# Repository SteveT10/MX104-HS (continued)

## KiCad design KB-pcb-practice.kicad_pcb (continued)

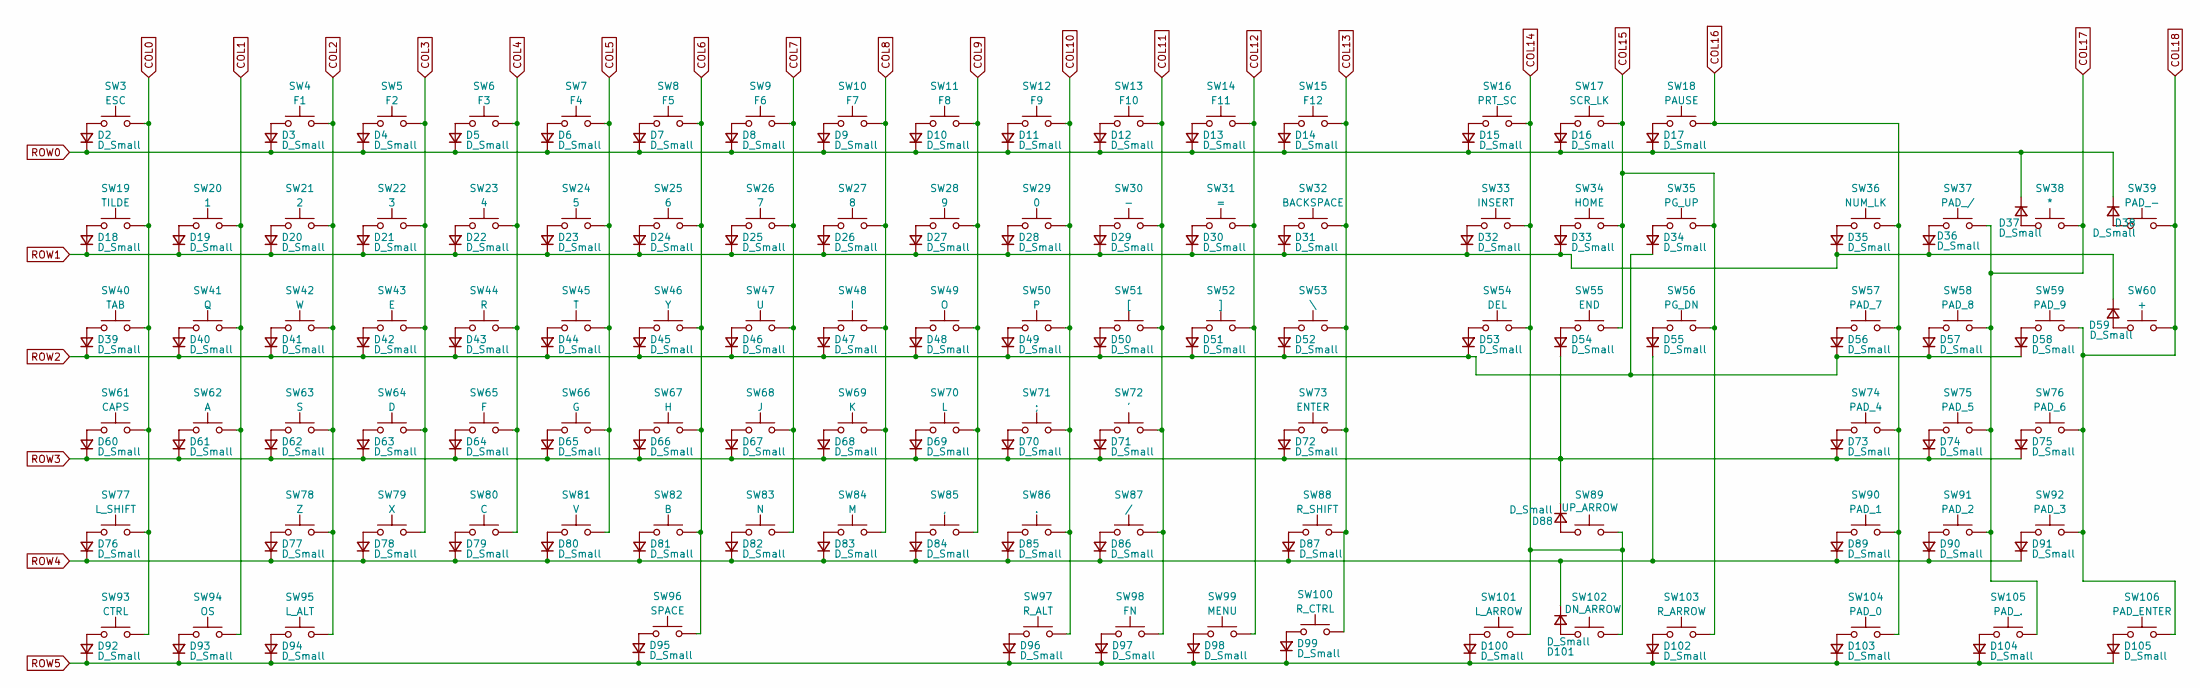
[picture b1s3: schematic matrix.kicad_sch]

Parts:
D2, D3, D4, D5, D6, D7, D8, D9, D10, D11, D12, D13, D14, D15, D16, D17, D18, D19, D20, D21, D22, D23, D24, D25, D26, D27, D28, D29, D30, D31, D32, D33, D34, D35, D36, D37, D38, D39, D40, D41, D42, D43, D44, D45, D46, D47, D48, D49, D50, D51, D52, D53, D54, D55, D56, D57, D58, D59, D60, D61, D62, D63, D64, D65, D66, D67, D68, D69, D70, D71, D72, D73, D74, D75, D76, D77, D78, D79, D80, D81, D82, D83, D84, D85, D86, D87, D88, D89, D90, D91, D92, D93, D94, D95, D96, D97, D98, D99, D100, D101, D102, D103, D104, D105: D_Small; D_SOD-123
SW3: ESC; MXOnly-1U-Hotswap
SW4: F1; MXOnly-1U-Hotswap
SW5: F2; MXOnly-1U-Hotswap
SW6: F3; MXOnly-1U-Hotswap
SW7: F4; MXOnly-1U-Hotswap
SW8: F5; MXOnly-1U-Hotswap
SW9: F6; MXOnly-1U-Hotswap
SW10: F7; MXOnly-1U-Hotswap
SW11: F8; MXOnly-1U-Hotswap
SW12: F9; MXOnly-1U-Hotswap
SW13: F10; MXOnly-1U-Hotswap
SW14: F11; MXOnly-1U-Hotswap
SW15: F12; MXOnly-1U-Hotswap
SW16: PRT_SC; MXOnly-1U-Hotswap
SW17: SCR_LK; MXOnly-1U-Hotswap
SW18: PAUSE; MXOnly-1U-Hotswap
SW19: TILDE; MXOnly-1U-Hotswap
SW20: 1; MXOnly-1U-Hotswap
SW21: 2; MXOnly-1U-Hotswap
SW22: 3; MXOnly-1U-Hotswap
SW23: 4; MXOnly-1U-Hotswap
SW24: 5; MXOnly-1U-Hotswap
SW25: 6; MXOnly-1U-Hotswap
SW26: 7; MXOnly-1U-Hotswap
SW27: 8; MXOnly-1U-Hotswap
SW28: 9; MXOnly-1U-Hotswap
SW29: 0; MXOnly-1U-Hotswap
SW30: -; MXOnly-1U-Hotswap
SW31: =; MXOnly-1U-Hotswap
SW32: BACKSPACE; MXOnly-2U-Hotswap
SW33: INSERT; MXOnly-1U-Hotswap
SW34: HOME; MXOnly-1U-Hotswap
SW35: PG_UP; MXOnly-1U-Hotswap
SW36: NUM_LK; MXOnly-1U-Hotswap
SW37: PAD_/; MXOnly-1U-Hotswap
SW38: *; MXOnly-1U-Hotswap
SW39: PAD_-; MXOnly-1U-Hotswap
SW40: TAB; MXOnly-1.5U-Hotswap
SW41: Q; MXOnly-1U-Hotswap
SW42: W; MXOnly-1U-Hotswap
SW43: E; MXOnly-1U-Hotswap
SW44: R; MXOnly-1U-Hotswap
SW45: T; MXOnly-1U-Hotswap
SW46: Y; MXOnly-1U-Hotswap
SW47: U; MXOnly-1U-Hotswap
SW48: I; MXOnly-1U-Hotswap
SW49: O; MXOnly-1U-Hotswap
SW50: P; MXOnly-1U-Hotswap
SW51: [; MXOnly-1U-Hotswap
SW52: ]; MXOnly-1U-Hotswap
SW53: \; MXOnly-1.5U-Hotswap
SW54: DEL; MXOnly-1U-Hotswap
SW55: END; MXOnly-1U-Hotswap
SW56: PG_DN; MXOnly-1U-Hotswap
SW57: PAD_7; MXOnly-1U-Hotswap
SW58: PAD_8; MXOnly-1U-Hotswap
SW59: PAD_9; MXOnly-1U-Hotswap
SW60: +; MXOnly-2U-Hotswap
SW61: CAPS; MXOnly-1.75U-Hotswap
SW62: A; MXOnly-1U-Hotswap
SW63: S; MXOnly-1U-Hotswap
SW64: D; MXOnly-1U-Hotswap
SW65: F; MXOnly-1U-Hotswap
SW66: G; MXOnly-1U-Hotswap
SW67: H; MXOnly-1U-Hotswap
SW68: J; MXOnly-1U-Hotswap
SW69: K; MXOnly-1U-Hotswap
SW70: L; MXOnly-1U-Hotswap
SW71: ;; MXOnly-1U-Hotswap
SW72: '; MXOnly-1U-Hotswap
SW73: ENTER; MXOnly-2.25U-Hotswap
SW74: PAD_4; MXOnly-1U-Hotswap
SW75: PAD_5; MXOnly-1U-Hotswap
SW76: PAD_6; MXOnly-1U-Hotswap
SW77: L_SHIFT; MXOnly-2.25U-Hotswap
SW78: Z; MXOnly-1U-Hotswap
SW79: X; MXOnly-1U-Hotswap
SW80: C; MXOnly-1U-Hotswap
SW81: V; MXOnly-1U-Hotswap
SW82: B; MXOnly-1U-Hotswap
SW83: N; MXOnly-1U-Hotswap
SW84: M; MXOnly-1U-Hotswap
SW85: ,; MXOnly-1U-Hotswap
SW86: .; MXOnly-1U-Hotswap
SW87: /; MXOnly-1U-Hotswap
SW88: R_SHIFT; MXOnly-2.75U-Hotswap
SW89: UP_ARROW; MXOnly-1U-Hotswap
SW90: PAD_1; MXOnly-1U-Hotswap
SW91: PAD_2; MXOnly-1U-Hotswap
SW92: PAD_3; MXOnly-1U-Hotswap
SW93: CTRL; MXOnly-1.25U-Hotswap
SW94: OS; MXOnly-1.25U-Hotswap
SW95: L_ALT; MXOnly-1.25U-Hotswap
SW96: SPACE; MXOnly-6.25U-Hotswap
SW97: R_ALT; MXOnly-1.25U-Hotswap
SW98: FN; MXOnly-1.25U-Hotswap
SW99: MENU; MXOnly-1.25U-Hotswap
SW100: R_CTRL; MXOnly-1.25U-Hotswap
SW101: L_ARROW; MXOnly-1U-Hotswap
SW102: DN_ARROW; MXOnly-1U-Hotswap
SW103: R_ARROW; MXOnly-1U-Hotswap
SW104: PAD_0; MXOnly-2U-Hotswap
SW105: PAD_.; MXOnly-1U-Hotswap
SW106: PAD_ENTER; MXOnly-2U-Hotswap

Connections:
COL0: SW3.2, SW19.2, SW40.2, SW61.2, SW77.2, SW93.2; also elsewhere on the board
COL1: SW20.2, SW41.2, SW62.2, SW94.2; also elsewhere on the board
COL2: SW4.2, SW21.2, SW42.2, SW63.2, SW78.2, SW95.2; also elsewhere on the board
COL3: SW5.2, SW22.2, SW43.2, SW64.2, SW79.2; also elsewhere on the board
COL4: SW6.2, SW23.2, SW44.2, SW65.2, SW80.2; also elsewhere on the board
COL5: SW7.2, SW24.2, SW45.2, SW66.2, SW81.2; also elsewhere on the board
COL6: SW8.2, SW25.2, SW46.2, SW67.2, SW82.2, SW96.2; also elsewhere on the board
COL7: SW9.2, SW26.2, SW47.2, SW68.2, SW83.2; also elsewhere on the board
COL8: SW10.2, SW27.2, SW48.2, SW69.2, SW84.2; also elsewhere on the board
COL9: SW11.2, SW28.2, SW49.2, SW70.2, SW85.2; also elsewhere on the board
COL10: SW12.2, SW29.2, SW50.2, SW71.2, SW86.2, SW97.2; also elsewhere on the board
COL11: SW13.2, SW30.2, SW51.2, SW72.2, SW87.2, SW98.2; also elsewhere on the board
COL12: SW14.2, SW31.2, SW52.2, SW99.2; also elsewhere on the board
COL13: SW15.2, SW32.2, SW53.2, SW73.2, SW88.2, SW100.2; also elsewhere on the board
COL14: SW16.2, SW33.2, SW54.2, SW89.2, SW101.2, SW102.2; also elsewhere on the board
COL15: SW17.2, SW34.2, SW35.2, SW55.2, SW56.2, SW103.2; also elsewhere on the board
COL16: SW18.2, SW36.2, SW57.2, SW74.2, SW90.2, SW104.2; also elsewhere on the board
COL17: SW37.2, SW38.2, SW58.2, SW75.2, SW91.2, SW105.2; also elsewhere on the board
COL18: SW39.2, SW59.2, SW60.2, SW76.2, SW92.2, SW106.2; also elsewhere on the board
unnamed: D2.2 (A), SW3.1
unnamed: D3.2 (A), SW4.1
unnamed: D4.2 (A), SW5.1
unnamed: D5.2 (A), SW6.1
unnamed: D6.2 (A), SW7.1
unnamed: D7.2 (A), SW8.1
unnamed: D8.2 (A), SW9.1
unnamed: D9.2 (A), SW10.1
unnamed: D10.2 (A), SW11.1
unnamed: D11.2 (A), SW12.1
unnamed: D12.2 (A), SW13.1
unnamed: D13.2 (A), SW14.1
unnamed: D14.2 (A), SW15.1
unnamed: D15.2 (A), SW16.1
unnamed: D16.2 (A), SW17.1
unnamed: D17.2 (A), SW18.1
unnamed: D18.2 (A), SW19.1
unnamed: D19.2 (A), SW20.1
unnamed: D20.2 (A), SW21.1
unnamed: D21.2 (A), SW22.1
unnamed: D22.2 (A), SW23.1
unnamed: D23.2 (A), SW24.1
unnamed: D24.2 (A), SW25.1
unnamed: D25.2 (A), SW26.1
unnamed: D26.2 (A), SW27.1
unnamed: D27.2 (A), SW28.1
unnamed: D28.2 (A), SW29.1
unnamed: D29.2 (A), SW30.1
unnamed: D30.2 (A), SW31.1
unnamed: D31.2 (A), SW32.1
unnamed: D32.2 (A), SW33.1
unnamed: D33.2 (A), SW34.1
unnamed: D34.2 (A), SW35.1
unnamed: D35.2 (A), SW36.1
unnamed: D36.2 (A), SW37.1
unnamed: D37.2 (A), SW38.1
unnamed: D38.2 (A), SW39.1
unnamed: D39.2 (A), SW40.1
unnamed: D40.2 (A), SW41.1
unnamed: D41.2 (A), SW42.1
unnamed: D42.2 (A), SW43.1
unnamed: D43.2 (A), SW44.1
unnamed: D44.2 (A), SW45.1
unnamed: D45.2 (A), SW46.1
unnamed: D46.2 (A), SW47.1
unnamed: D47.2 (A), SW48.1
unnamed: D48.2 (A), SW49.1
unnamed: D49.2 (A), SW50.1
unnamed: D50.2 (A), SW51.1
unnamed: D51.2 (A), SW52.1
unnamed: D52.2 (A), SW53.1
unnamed: D53.2 (A), SW54.1
unnamed: D54.2 (A), SW55.1
unnamed: D55.2 (A), SW56.1
unnamed: D56.2 (A), SW57.1
unnamed: D57.2 (A), SW58.1
unnamed: D58.2 (A), SW59.1
unnamed: D59.2 (A), SW60.1
unnamed: D60.2 (A), SW61.1
unnamed: D61.2 (A), SW62.1
unnamed: D62.2 (A), SW63.1
unnamed: D63.2 (A), SW64.1
unnamed: D64.2 (A), SW65.1
unnamed: D65.2 (A), SW66.1
unnamed: D66.2 (A), SW67.1
unnamed: D67.2 (A), SW68.1
unnamed: D68.2 (A), SW69.1
unnamed: D69.2 (A), SW70.1
unnamed: D70.2 (A), SW71.1
unnamed: D71.2 (A), SW72.1
unnamed: D72.2 (A), SW73.1
unnamed: D73.2 (A), SW74.1
unnamed: D74.2 (A), SW75.1
unnamed: D75.2 (A), SW76.1
unnamed: D76.2 (A), SW77.1
unnamed: D77.2 (A), SW78.1
unnamed: D78.2 (A), SW79.1
unnamed: D79.2 (A), SW80.1
unnamed: D80.2 (A), SW81.1
unnamed: D81.2 (A), SW82.1
unnamed: D82.2 (A), SW83.1
unnamed: D83.2 (A), SW84.1
unnamed: D84.2 (A), SW85.1
unnamed: D85.2 (A), SW86.1
unnamed: D86.2 (A), SW87.1
unnamed: D87.2 (A), SW88.1
unnamed: D88.2 (A), SW89.1
unnamed: D89.2 (A), SW90.1
unnamed: D90.2 (A), SW91.1
unnamed: D91.2 (A), SW92.1
unnamed: D92.2 (A), SW93.1
unnamed: D93.2 (A), SW94.1
unnamed: D94.2 (A), SW95.1
unnamed: D95.2 (A), SW96.1
unnamed: D96.2 (A), SW97.1
unnamed: D97.2 (A), SW98.1
unnamed: D98.2 (A), SW99.1
unnamed: D99.2 (A), SW100.1
unnamed: D100.2 (A), SW101.1
unnamed: D101.2 (A), SW102.1
unnamed: D102.2 (A), SW103.1
unnamed: D103.2 (A), SW104.1
unnamed: D104.2 (A), SW105.1
unnamed: D105.2 (A), SW106.1
ROW0: D2.1 (K), D3.1 (K), D4.1 (K), D5.1 (K), D6.1 (K), D7.1 (K), D8.1 (K), D9.1 (K), D10.1 (K), D11.1 (K), D12.1 (K), D13.1 (K), D14.1 (K), D15.1 (K), D16.1 (K), D17.1 (K), D37.1 (K), D38.1 (K); also elsewhere on the board
ROW1: D18.1 (K), D19.1 (K), D20.1 (K), D21.1 (K), D22.1 (K), D23.1 (K), D24.1 (K), D25.1 (K), D26.1 (K), D27.1 (K), D28.1 (K), D29.1 (K), D30.1 (K), D31.1 (K), D32.1 (K), D33.1 (K), D35.1 (K), D36.1 (K), D59.1 (K); also elsewhere on the board
ROW2: D34.1 (K), D39.1 (K), D40.1 (K), D41.1 (K), D42.1 (K), D43.1 (K), D44.1 (K), D45.1 (K), D46.1 (K), D47.1 (K), D48.1 (K), D49.1 (K), D50.1 (K), D51.1 (K), D52.1 (K), D53.1 (K), D56.1 (K), D57.1 (K), D58.1 (K); also elsewhere on the board
ROW3: D54.1 (K), D60.1 (K), D61.1 (K), D62.1 (K), D63.1 (K), D64.1 (K), D65.1 (K), D66.1 (K), D67.1 (K), D68.1 (K), D69.1 (K), D70.1 (K), D71.1 (K), D72.1 (K), D73.1 (K), D74.1 (K), D75.1 (K), D88.1 (K); also elsewhere on the board
ROW4: D55.1 (K), D76.1 (K), D77.1 (K), D78.1 (K), D79.1 (K), D80.1 (K), D81.1 (K), D82.1 (K), D83.1 (K), D84.1 (K), D85.1 (K), D86.1 (K), D87.1 (K), D89.1 (K), D90.1 (K), D91.1 (K), D101.1 (K); also elsewhere on the board
ROW5: D92.1 (K), D93.1 (K), D94.1 (K), D95.1 (K), D96.1 (K), D97.1 (K), D98.1 (K), D99.1 (K), D100.1 (K), D102.1 (K), D103.1 (K), D104.1 (K), D105.1 (K); also elsewhere on the board

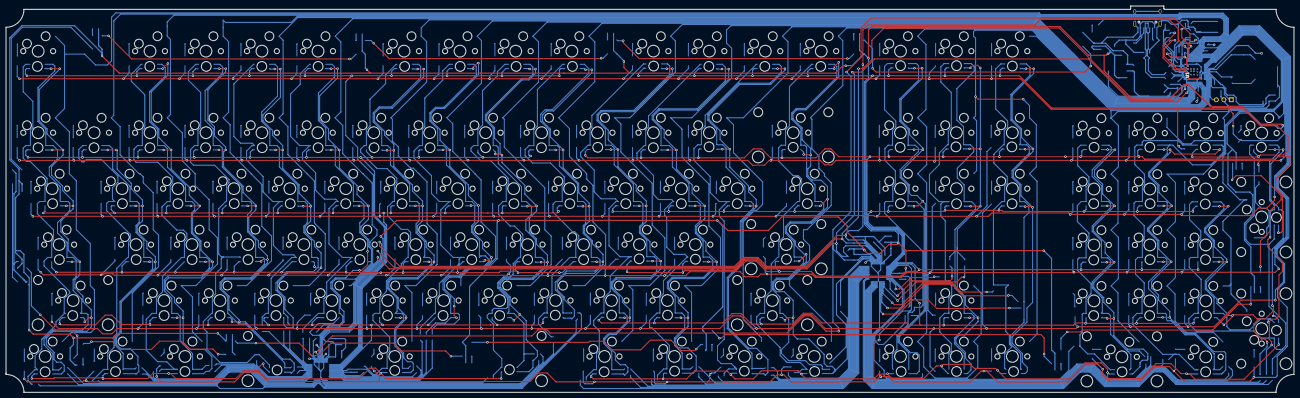
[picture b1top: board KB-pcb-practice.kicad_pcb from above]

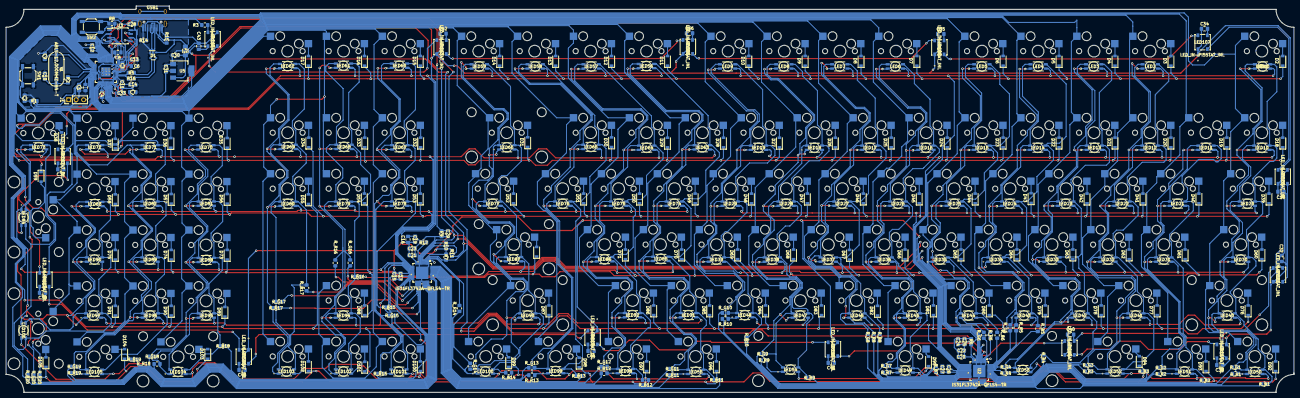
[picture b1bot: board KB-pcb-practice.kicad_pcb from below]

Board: 2 copper layers, 438.7 x 131.6 mm, 459 parts (355 on the bottom side), 306 nets.

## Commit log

2023-03-13 Setting up
    Created a new github repository and started new project in local folder. Located in documents/github.
2023-03-13 Added submodules
2023-03-13 Added footprint libraries
    Opened Pcb file, added each lib's .pretty folder to project specific libraries.
2023-03-14 Day 1 work on schematic
    Added Decoupling capacitors and MCU to schematic.
2023-03-19 Save before adding libraries from UL
    Before downloading and adding UL components
2023-03-20 Added Clock Circuit to Sch
2023-03-20 Added reset circuit and Quad SPI Flash
2023-03-20 Move lib location
2023-03-20 testing submodules
2023-03-20 Revert back
2023-03-20 Revert "Revert back"
    This reverts commit 38241fb76374d2e541cf47fd2185290756325f6b.
2023-03-20 Revert "testing submodules"
    This reverts commit 86c78e3f3850c6d0b9f56e0e32bc27ca20c184e0.
2023-03-20 Revert "Move lib location"
    This reverts commit a62a4a7883b50f9c587de4e9ec7890213ab8f2a7.
2023-03-20 Updated .gitmodules
2023-03-20 Added USB C header submodule
2023-03-20 Mostly Finished Schematic
    Still looking for switches for reset and flash circuit.
2023-03-30 Added SWD circuit, began RGB matrix
2023-04-01 Started work on Led sch,
    Decided on led driver IC
    Decided on led part
    started work on led matrix
2023-04-08 Changed led driver
2023-04-12 Finished Electric Schematic Of Keyboard
    All components are now wired. Positions for spacers, button stabilizers, and threated holes not accounted.
2023-04-13 Started work on PCB layout
    Slightly Adjusted electric schematic as well.
2023-04-14 Changing hotswap switches
    Reverse Mount leds not added yet.
2023-04-14 Changed to reverse mount rgb leds
    Both symbol and footprint were changed accordingly.
2023-04-19 MCU pins all routed
    Just need to finish led drivers and connect matrix
2023-04-19 Updated Schematic to match previous
2023-04-24 Started Routing LED Drivers
2023-04-25 Began Routing Columns and Rows
2023-04-25 Right LED Driver almost connected
2023-04-26 Routing Finished
2023-05-04 Revising for underglow and PD IC
2023-05-08 Rearranged LED Drivers
2023-05-09 Fixed Majority of Errors in ERC
2023-05-10 Added RGB Underglow
2023-05-11 Fixed Errors Relating to edge cuts
2023-06-14 Added fill zones and some art to PCB
2023-06-14 Added media folder and photos of Sch and PCB
2023-06-18 Reorganized Files
2023-06-18 Updated submodules
2023-06-18 slight change to lib
2023-07-02 Began changing out backlight for better components
2023-07-06 Finished version 1.0
2023-07-25 Added README.md
2023-07-25 Create LICENSE
2023-08-11 Started QMK files
2023-08-24 Updated QMK files
